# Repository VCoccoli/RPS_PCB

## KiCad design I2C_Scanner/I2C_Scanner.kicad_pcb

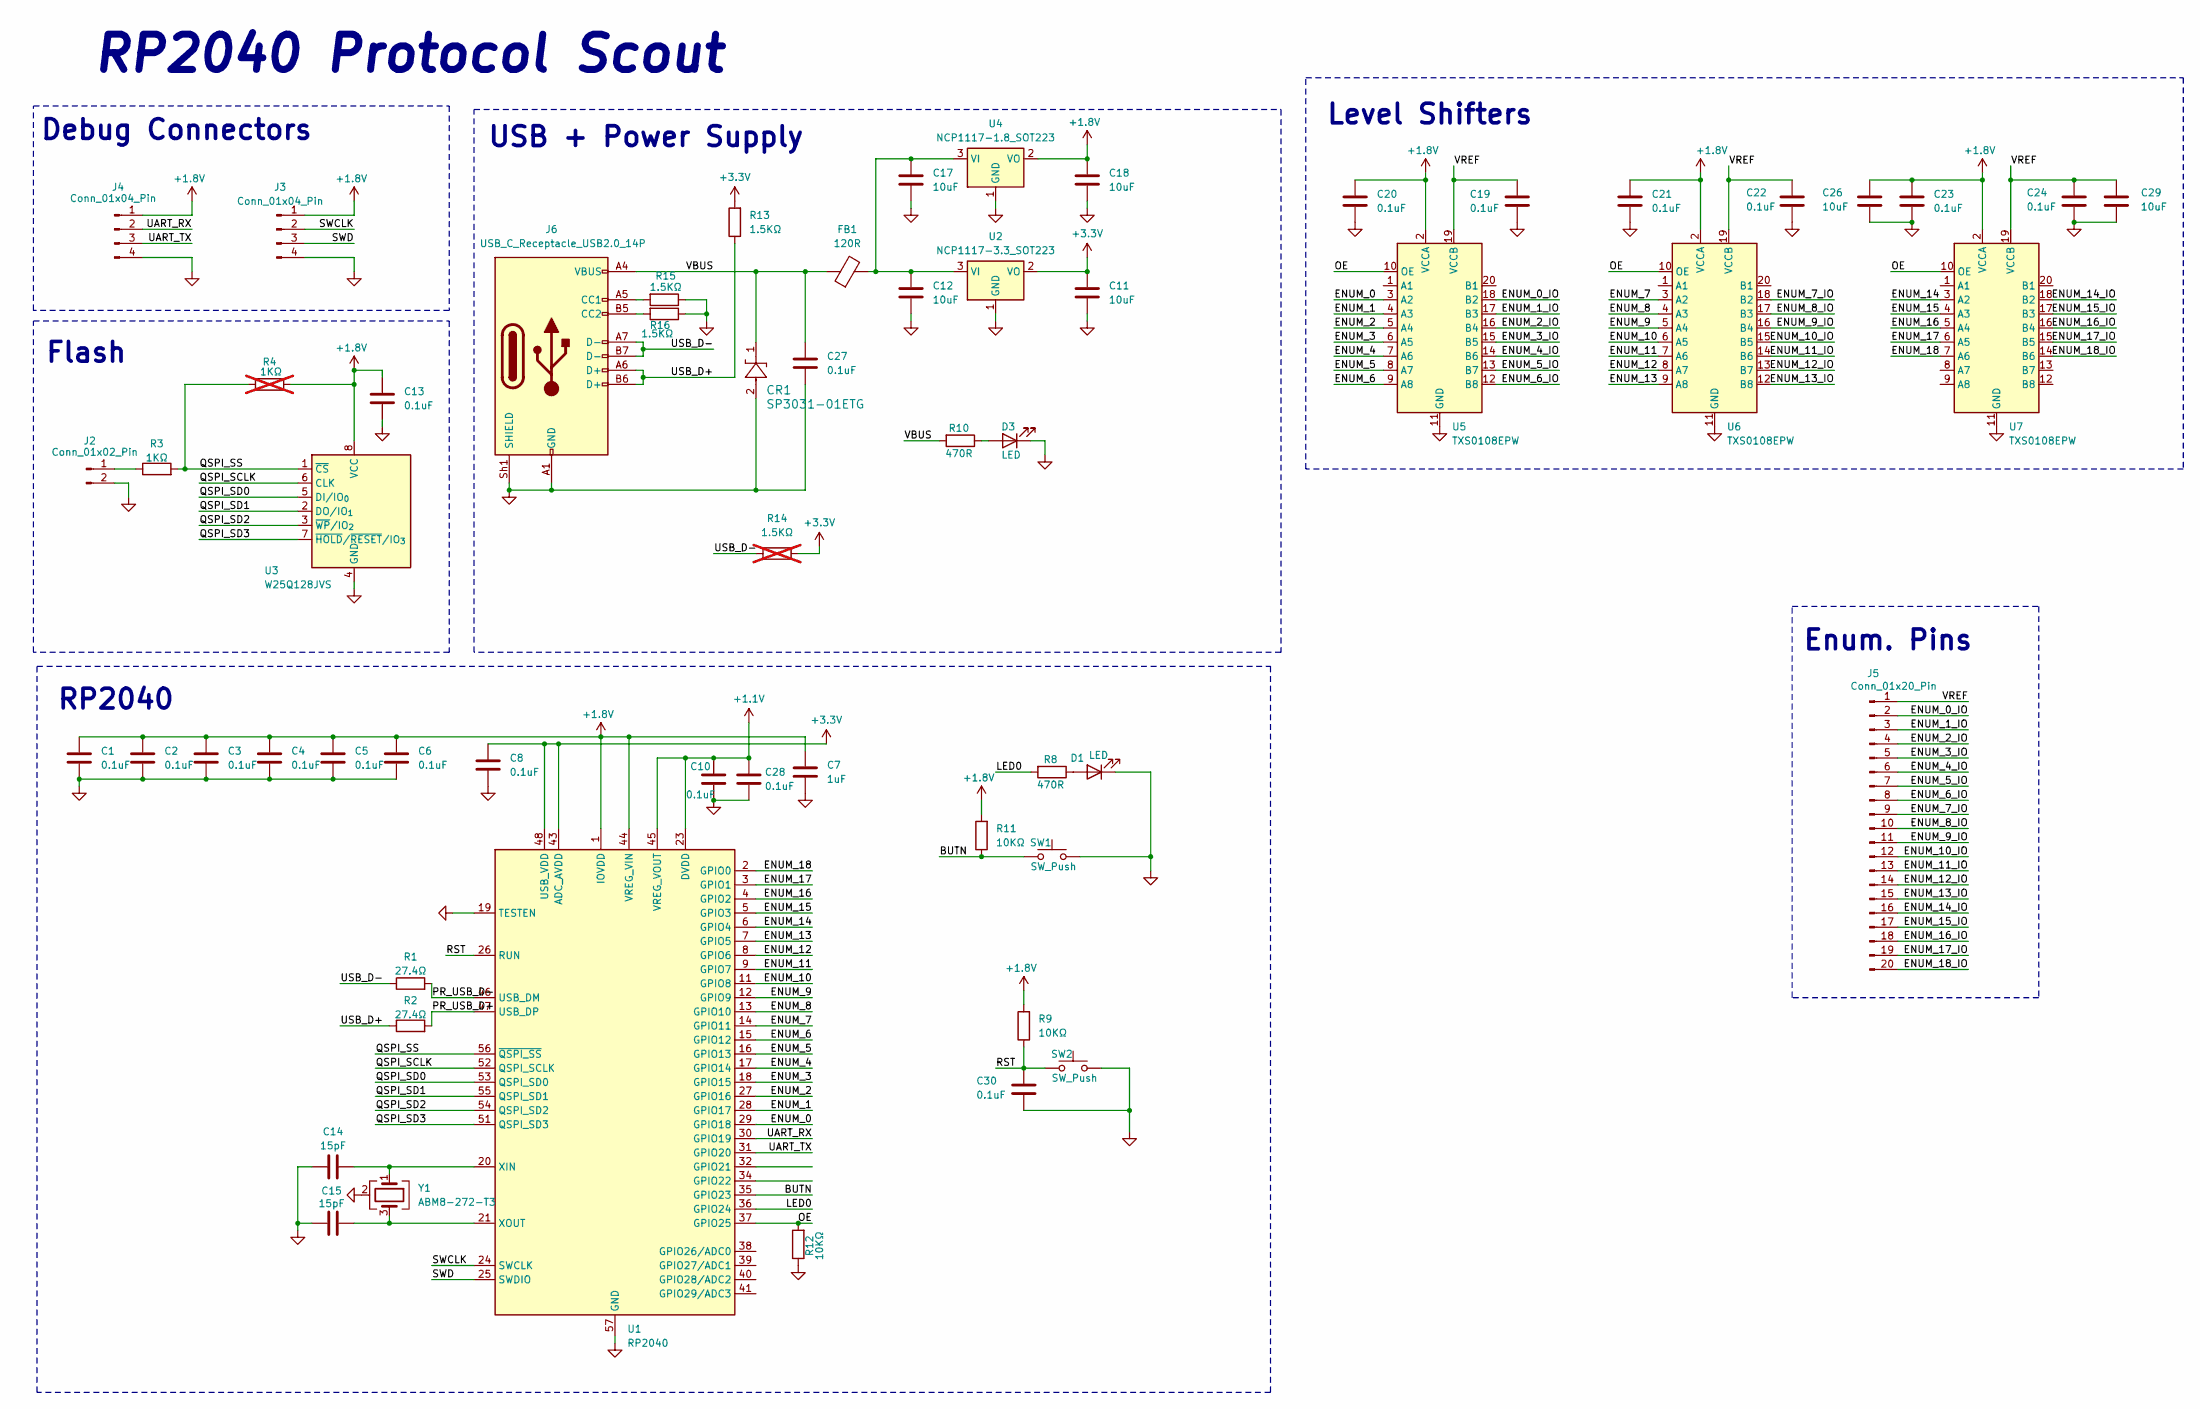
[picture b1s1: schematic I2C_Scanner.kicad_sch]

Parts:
C1, C2, C3, C4, C5, C6, C8, C10, C13, C19, C20, C21, C22, C23, C24, C27, C28, C30: 0.1uF; C_0402_1005Metric
C7: 1uF; C_0402_1005Metric
C11, C12, C17, C18, C26, C29: 10uF; C_0603_1608Metric
C14, C15: 15pF; C_0402_1005Metric
CR1: SP3031-01ETG; SOD882_LTF
D1, D3: LED; LED_0402_1005Metric
FB1: 120R; LED_0805_2012Metric
J2: Conn_01x02_Pin; PinHeader_1x02_P2.54mm_Vertical
J3, J4: Conn_01x04_Pin; PinHeader_1x04_P2.54mm_Vertical
J5: Conn_01x20_Pin; PinHeader_2x10_P2.54mm_Vertical
J6: USB_C_Receptacle_USB2.0_14P; TYPE-C-31-M-14
R1, R2: 27.4Ω; R_0402_1005Metric
R3: 1KΩ; R_0402_1005Metric
R4: 1KΩ; R_0402_1005Metric; not fitted
R8, R10: 470R; R_0805_2012Metric
R9, R11, R12: 10KΩ; R_0402_1005Metric
R13, R15, R16: 1.5KΩ; R_0402_1005Metric
R14: 1.5KΩ; R_0805_2012Metric; not fitted
SW1, SW2: SW_Push; SW_Push_1P1T_NO_CK_KMR2
U1: RP2040; QFN-56-1EP_7x7mm_P0.4mm_EP3.2x3.2mm
U2: NCP1117-3.3_SOT223; SOT-223-3_TabPin2
U3: W25Q128JVS; SOIC-8_5.3x5.3mm_P1.27mm
U4: NCP1117-1.8_SOT223; SOT-223-3_TabPin2
U5, U6, U7: TXS0108EPW; TSSOP-20_4.4x6.5mm_P0.65mm
Y1: ABM8-272-T3; Crystal_SMD_3225-4Pin_3.2x2.5mm

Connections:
+1.1V: C10.1, C28.1, U1.23 (DVDD), U1.45 (VREG_VOUT), U1.50 (DVDD)
+1.8V: C1.1, C2.1, C3.1, C4.1, C5.1, C6.1, C7.1, C13.1, C18.1, C20.1, C21.1, C23.1, C26.1, J3.1, J4.1, R4.2, R9.2, R11.2, U1.1 (IOVDD), U1.10 (IOVDD), U1.22 (IOVDD), U1.33 (IOVDD), U1.42 (IOVDD), U1.44 (VREG_VIN), U1.49 (IOVDD), U3.8 (VCC), U4.2 (VO), U5.2 (VCCA), U6.2 (VCCA), U7.2 (VCCA)
+3.3V: C8.1, C11.1, R13.2, R14.1, U1.43 (ADC_AVDD), U1.48 (USB_VDD), U2.2 (VO); also elsewhere on the board
/BUTN: R11.1, SW1.1, U1.35 (GPIO23)
/ENUM_0: U1.29 (GPIO18), U5.3 (A2)
/ENUM_0_IO: J5.2, U5.18 (B2)
/ENUM_1: U1.28 (GPIO17), U5.4 (A3)
/ENUM_1_IO: J5.3, U5.17 (B3)
/ENUM_2: U1.27 (GPIO16), U5.5 (A4)
/ENUM_2_IO: J5.4, U5.16 (B4)
/ENUM_3: U1.18 (GPIO15), U5.6 (A5)
/ENUM_3_IO: J5.5, U5.15 (B5)
/ENUM_4: U1.17 (GPIO14), U5.7 (A6)
/ENUM_4_IO: J5.6, U5.14 (B6)
/ENUM_5: U1.16 (GPIO13), U5.8 (A7)
/ENUM_5_IO: J5.7, U5.13 (B7)
/ENUM_6: U1.15 (GPIO12), U5.9 (A8)
/ENUM_6_IO: J5.8, U5.12 (B8)
/ENUM_7: U1.14 (GPIO11), U6.3 (A2)
/ENUM_7_IO: J5.9, U6.18 (B2)
/ENUM_8: U1.13 (GPIO10), U6.4 (A3)
/ENUM_8_IO: J5.10, U6.17 (B3)
/ENUM_9: U1.12 (GPIO9), U6.5 (A4)
/ENUM_9_IO: J5.11, U6.16 (B4)
/ENUM_10: U1.11 (GPIO8), U6.6 (A5)
/ENUM_10_IO: J5.12, U6.15 (B5)
/ENUM_11: U1.9 (GPIO7), U6.7 (A6)
/ENUM_11_IO: J5.13, U6.14 (B6)
/ENUM_12: U1.8 (GPIO6), U6.8 (A7)
/ENUM_12_IO: J5.14, U6.13 (B7)
/ENUM_13: U1.7 (GPIO5), U6.9 (A8)
/ENUM_13_IO: J5.15, U6.12 (B8)
/ENUM_14: U1.6 (GPIO4), U7.3 (A2)
/ENUM_14_IO: J5.16, U7.18 (B2)
/ENUM_15: U1.5 (GPIO3), U7.4 (A3)
/ENUM_15_IO: J5.17, U7.17 (B3)
/ENUM_16: U1.4 (GPIO2), U7.5 (A4)
/ENUM_16_IO: J5.18, U7.16 (B4)
/ENUM_17: U1.3 (GPIO1), U7.6 (A5)
/ENUM_17_IO: J5.19, U7.15 (B5)
/ENUM_18: U1.2 (GPIO0), U7.7 (A6)
/ENUM_18_IO: J5.20, U7.14 (B6)
/LED0: R8.2, U1.36 (GPIO24)
/OE: R12.2, U1.37 (GPIO25), U5.10 (OE), U6.10 (OE), U7.10 (OE)
/PR_USB_D+: R2.2, U1.47 (USB_DP)
/PR_USB_D-: R1.2, U1.46 (USB_DM)
/QSPI_SCLK: U1.52 (QSPI_SCLK), U3.6 (CLK)
/QSPI_SD0: U1.53 (QSPI_SD0), U3.5 (DI/IO_{0})
/QSPI_SD1: U1.55 (QSPI_SD1), U3.2 (DO/IO_{1})
/QSPI_SD2: U1.54 (QSPI_SD2), U3.3 (~WP/IO_{2})
/QSPI_SD3: U1.51 (QSPI_SD3), U3.7 (~HOLD/~RESET/IO_{3})
/QSPI_SS: R3.2, R4.1, U1.56 (~QSPI_SS), U3.1 (~CS)
/RST: C30.1, R9.1, SW2.1, U1.26 (RUN)
/SWCLK: J3.2, U1.24 (SWCLK)
/SWD: J3.3, U1.25 (SWDIO)
/UART_RX: J4.2, U1.30 (GPIO19)
/UART_TX: J4.3, U1.31 (GPIO20)
/USB_D+: J6.A6 (D+), J6.B6 (D+), R2.1, R13.1
/USB_D-: J6.A7 (D-), J6.B7 (D-), R1.1, R14.2
/VBUS: C27.1, CR1.1, FB1.1, J6.A4 (VBUS), J6.A9 (VBUS), J6.B4 (VBUS), J6.B9 (VBUS), R10.2
/VREF: C19.1, C22.1, C24.1, C29.1, J5.1, U5.19 (VCCB), U6.19 (VCCB), U7.19 (VCCB)
GND: C1.2, C2.2, C3.2, C4.2, C5.2, C6.2, C7.2, C8.2, C10.2, C11.2, C12.2, C13.2, C14.1, C15.1, C17.2, C18.2, C19.2, C20.2, C21.2, C22.2, C23.2, C24.2, C26.2, C27.2, C28.2, C29.2, C30.2, CR1.2, D1.1 (K), D3.1 (K), J2.2, J3.4, J4.4, J6.A1 (GND), J6.A12 (GND), J6.B1 (GND), J6.B12 (GND), J6.Sh1 (SHIELD), R12.1, R15.1, R16.1, SW1.2, SW2.2, U1.19 (TESTEN), U1.57 (GND), U2.1 (GND), U3.4 (GND), U4.1 (GND), U5.11 (GND), U6.11 (GND), U7.11 (GND), Y1.2 (G), Y1.4 (G); also elsewhere on the board
unnamed: D1.2 (A), R8.1
unnamed: D3.2 (A), R10.1
unnamed: J2.1, R3.1
unnamed: J6.A5 (CC1), R15.2
unnamed: J6.B5 (CC2), R16.2
unnamed: C14.2, U1.20 (XIN), Y1.1
unnamed: C15.2, U1.21 (XOUT), Y1.3
unnamed: C12.1, C17.1, FB1.2, U2.3 (VI), U4.3 (VI)

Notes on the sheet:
RP2040
Level Shifters
USB + Power Supply
Flash
Enum. Pins
Debug Connectors
RP2040 Protocol Scout

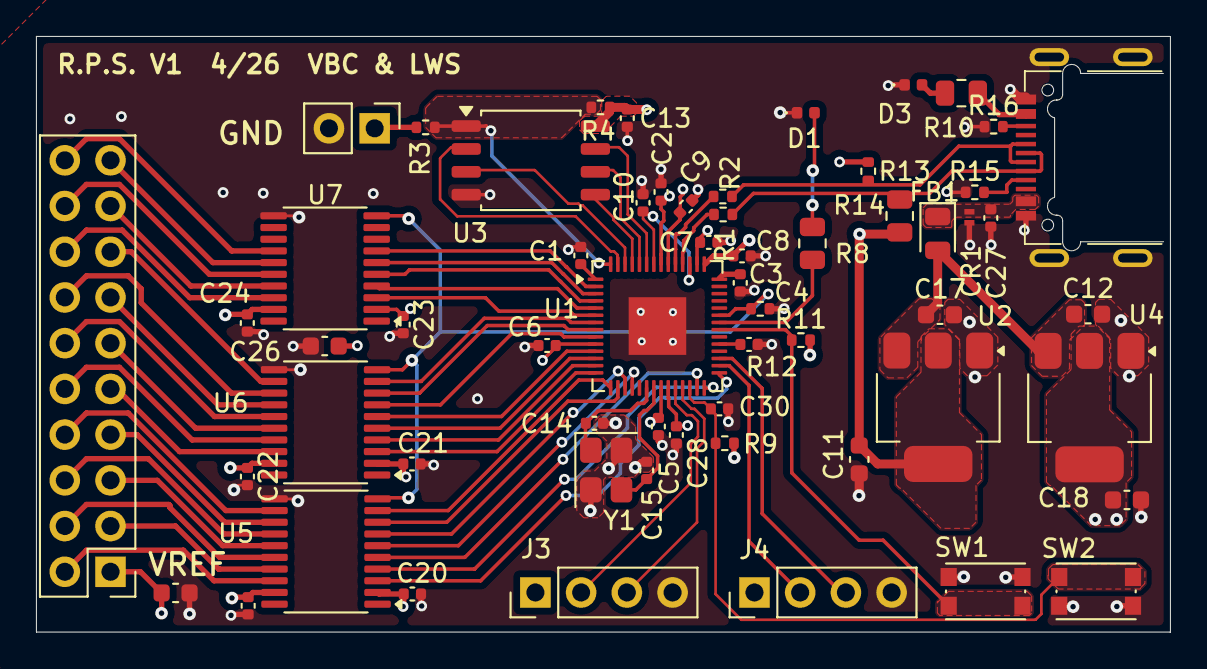
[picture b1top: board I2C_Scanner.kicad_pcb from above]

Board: 4 copper layers, 63.0 x 33.1 mm, 60 parts (0 on the bottom side), 70 nets.

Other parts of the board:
C9: 0.1uF; C_0402_1005Metric

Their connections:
+3.3V: C9.1; also elsewhere on the board
GND: C9.2; also elsewhere on the board

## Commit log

2026-06-05 v0.2
2026-06-06 RPS V2 proj Creation
2026-06-10 Added USB C
2026-06-10 Added Contributer Name
2026-06-10 Added Contributor Name
2026-06-10 Changed CC Resitor Values
